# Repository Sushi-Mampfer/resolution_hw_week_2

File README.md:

# Resolution hardware week 2

A reindeer with 3 leds that oscillate

---

## Simulation

I think I know how it works but every time I try to change something it breaks(but at least this exact version work).

[Link to Demo](https://falstad.com/circuit/circuitjs.html?ctz=CQAgjCAMB0l3BWcMBMcUHYMGZIA4UA2ATmIxAUgpABZsKBTAWjDACgAlcFPEYwvgP5QRNKkiqToCNgCduvYWB7hCkkNlxyQKFDUE69q9WHhsAxof1g1C47Six4EGIR4IaYvJDBlCGFGJHOBc2AHc7YV19YUg2ABd7PSplXmSRF2hCBBRsG2zsPzyPR0I8VLwEMGw8Al9K5CoAEwYAMwBDAFcAG3jwuxsUlWioNhsUOxQEAVSNNB0QFo6e+KZuhibwESkfNgBzO2x52ewy7f2dabmqKYFT3kkxt0uBW5frhaWu3rWNrfUYLsIm9hNgcgY4pYwRNBu9YfpAc4QCxoDQiDhAlMsOVNA8nKF5NCDETYSkzPIQa8rqSNFoDjV9EcqAyNGdHuMNHh9G8WUzPm1vqt1psXNtYOwIizhDRvBCLLRZbCWfDgkimKhsDhNcQxJBcmhshNEQSFVRpYrbGS4NopXcufZmVpgdTbG8RnFJfalfb3f0RlErrF+kTQfag4kRuk3WIMqVxjliMpCKxKJABK4MJBiFMwFgiMQs5ByKZmgKVgkNOD0iz0ilkShoLgxPxob4wDKwY5cp5MGVCLhKpAEGRGosy71+rD0jKUpa-UYp0Za8HwUqqzG4kA)

---
## Schematic

## PCB

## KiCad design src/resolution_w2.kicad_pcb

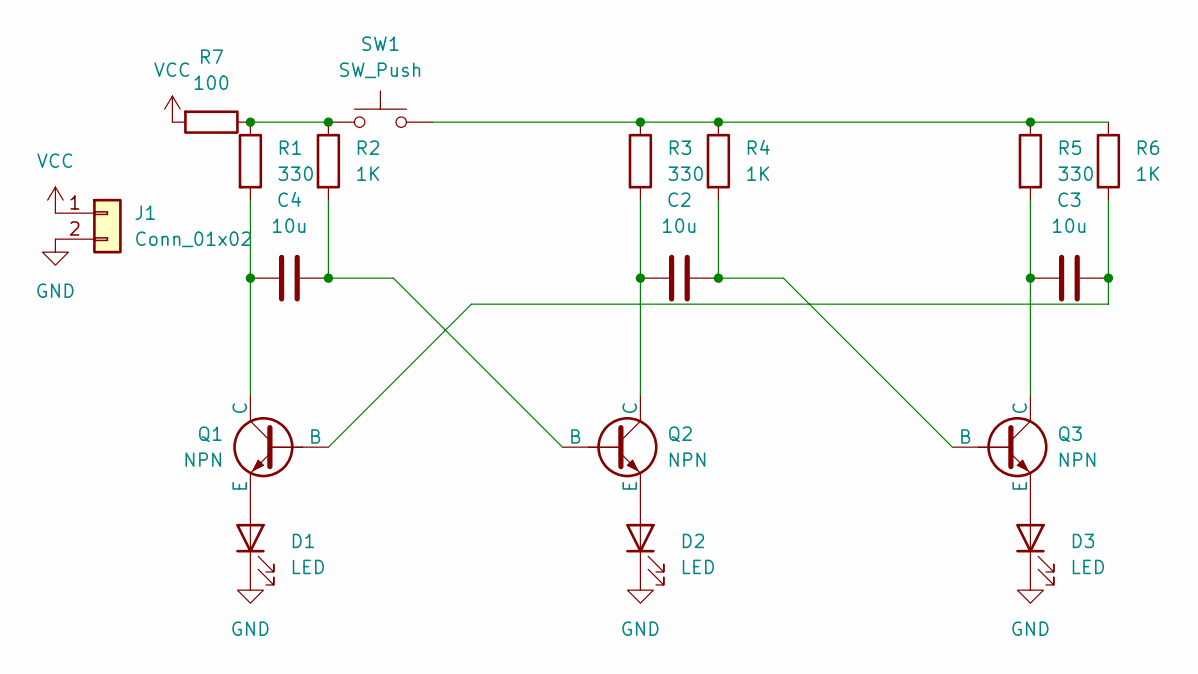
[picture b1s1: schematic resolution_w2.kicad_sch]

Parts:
C2, C3, C4: 10u; C_Disc_D5.0mm_W2.5mm_P5.00mm
D1, D2, D3: LED; LED_D5.0mm
J1: Conn_01x02; PinHeader_1x02_P2.54mm_Vertical
Q1, Q2, Q3: NPN; TO-92L_Inline_Wide
R1, R3, R5: 330; R_Axial_DIN0204_L3.6mm_D1.6mm_P7.62mm_Horizontal
R2, R4, R6: 1K; R_Axial_DIN0204_L3.6mm_D1.6mm_P7.62mm_Horizontal
R7: 100; R_Axial_DIN0204_L3.6mm_D1.6mm_P7.62mm_Horizontal
SW1: SW_Push; SW_PUSH_6mm

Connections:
GND: D1.1 (K), D2.1 (K), D3.1 (K), J1.2
unnamed: D1.2 (A), Q1.3 (E)
unnamed: D2.2 (A), Q2.3 (E)
unnamed: D3.2 (A), Q3.3 (E)
unnamed: C3.1, Q1.2 (B), R6.2
unnamed: C4.2, Q1.1 (C), R1.2
unnamed: C4.1, Q2.2 (B), R2.2
unnamed: C2.2, Q2.1 (C), R3.2
unnamed: C2.1, Q3.2 (B), R4.2
unnamed: C3.2, Q3.1 (C), R5.2
unnamed: R1.1, R2.1, R7.1, SW1.1
unnamed: R3.1, R4.1, R5.1, R6.1, SW1.2
VCC: J1.1, R7.2

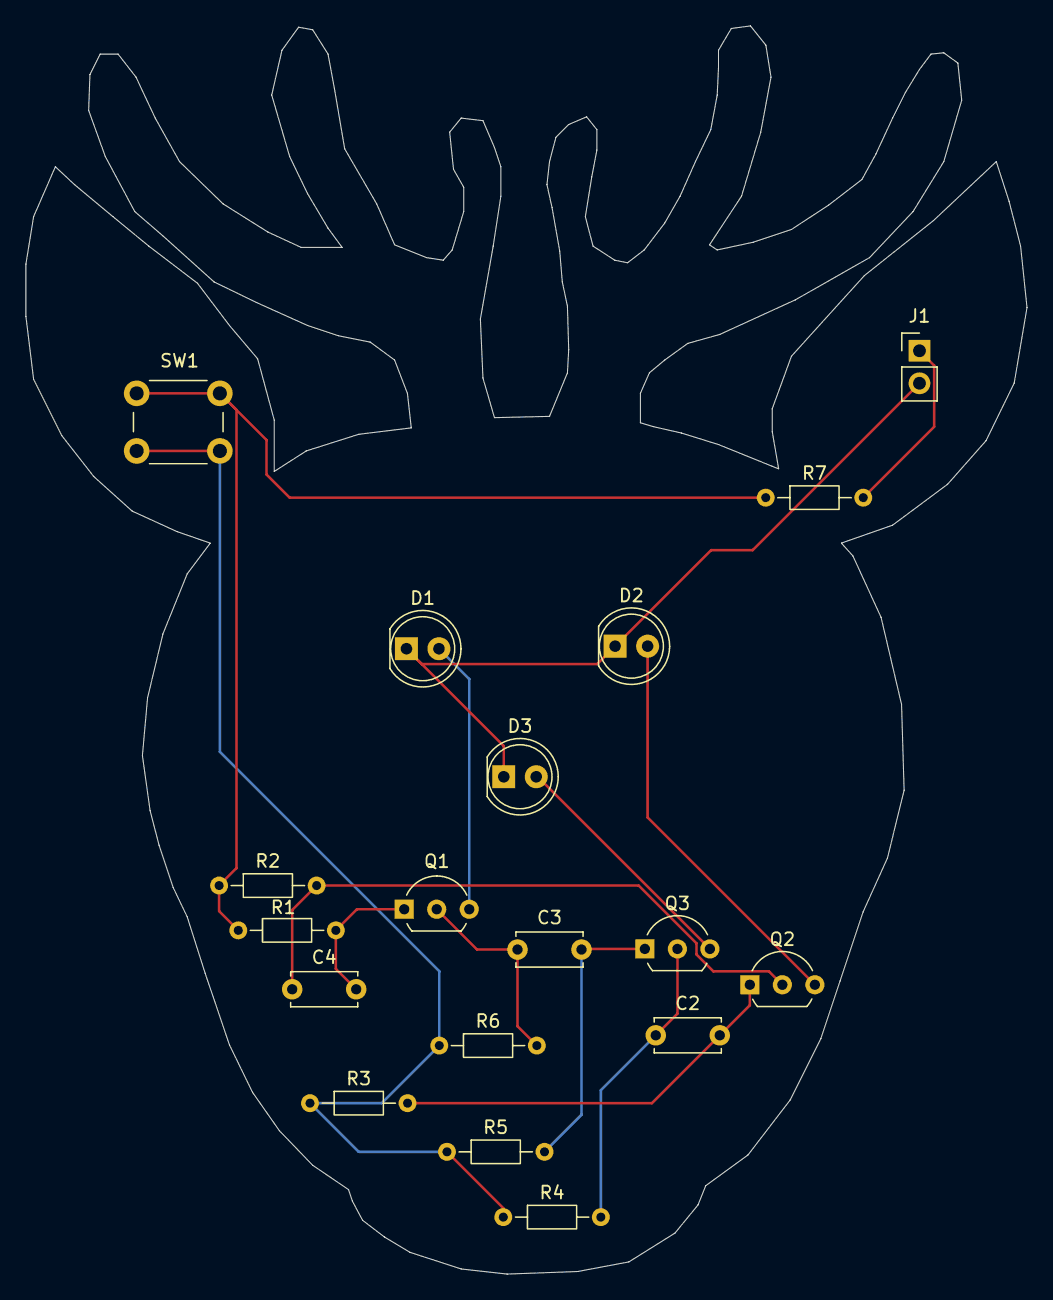
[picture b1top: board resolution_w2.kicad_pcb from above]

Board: 2 copper layers, 78.2 x 97.5 mm, 18 parts (0 on the bottom side), 13 nets.

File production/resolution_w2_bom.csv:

Designator,Footprint,Quantity,Value,LCSC Part #
"C2, C3, C4",C_Disc_D5.0mm_W2.5mm_P5.00mm,3,10u,
"D1, D2, D3",LED_D5.0mm,3,LED,
J1,PinHeader_1x02_P2.54mm_Vertical,1,Conn_01x02,
"Q1, Q2, Q3",TO-92L_Inline_Wide,3,NPN,
"R1, R3, R5",R_Axial_DIN0204_L3.6mm_D1.6mm_P7.62mm_Horizontal,3,330,
"R2, R4, R6",R_Axial_DIN0204_L3.6mm_D1.6mm_P7.62mm_Horizontal,3,1K,
R7,R_Axial_DIN0204_L3.6mm_D1.6mm_P7.62mm_Horizontal,1,100,
SW1,SW_PUSH_6mm,1,SW_Push,

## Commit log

2026-03-24 part 1
2026-03-25 production folder
2026-03-25 Add falstad.txt with circuit configuration data
2026-03-25 Add journal entries for circuit project updates
    Documented progress on circuit projects, including challenges and solutions.
2026-03-25 Dates fixed
2026-03-29 More details
2026-03-29 Added image
